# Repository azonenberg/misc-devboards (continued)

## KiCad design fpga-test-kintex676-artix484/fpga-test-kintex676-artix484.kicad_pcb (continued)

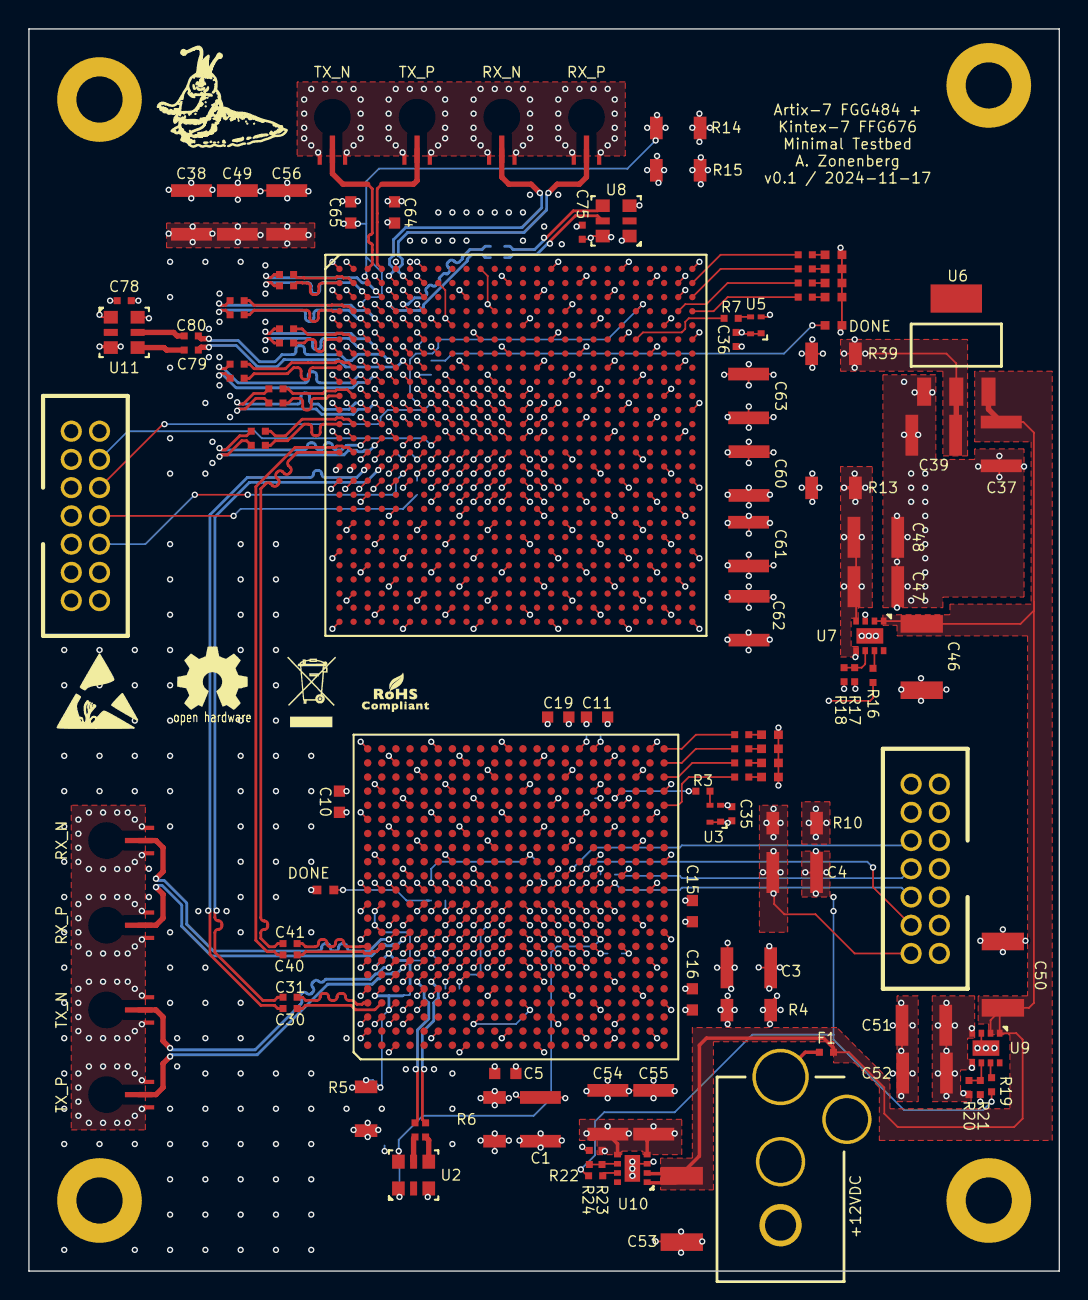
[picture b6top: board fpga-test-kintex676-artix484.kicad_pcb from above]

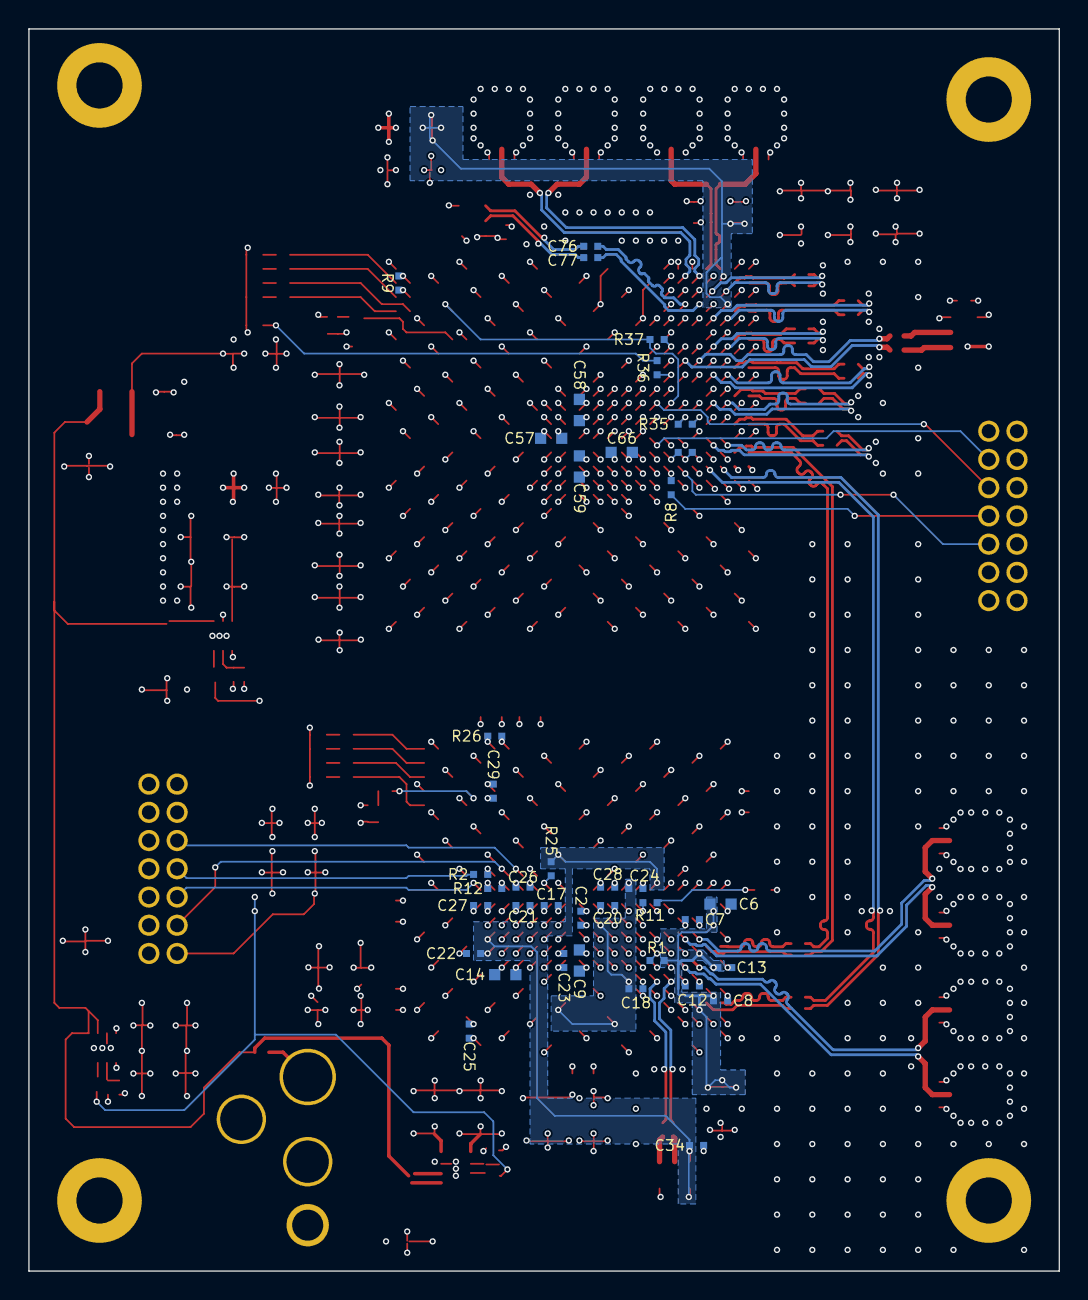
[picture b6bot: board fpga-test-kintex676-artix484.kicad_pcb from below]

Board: 4 copper layers, 73.0 x 88.0 mm, 161 parts (39 on the bottom side), 115 nets.

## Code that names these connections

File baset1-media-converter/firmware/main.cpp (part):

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void InitUART()
{
	//Initialize the UART
	static GPIOPin uart_tx(&GPIOA, 2,	GPIOPin::MODE_PERIPHERAL, 1);
	static GPIOPin uart_rx(&GPIOA, 3, GPIOPin::MODE_PERIPHERAL, 1);
	static UART uart(&USART1, &USART1, 417);
	g_uart = &uart;

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
void InitLEDs()
{
	GPIOPin gpio_led0(&GPIOA, 15, GPIOPin::MODE_OUTPUT);
	GPIOPin gpio_led1(&GPIOB, 3, GPIOPin::MODE_OUTPUT);
	GPIOPin gpio_led2(&GPIOB, 4, GPIOPin::MODE_OUTPUT);
	GPIOPin gpio_led3(&GPIOB, 5, GPIOPin::MODE_OUTPUT);
	gpio_led0 = 0;
	gpio_led1 = 0;
	gpio_led2 = 0;
	gpio_led3 = 0;

	g_led[0] = &gpio_led0;
	g_led[1] = &gpio_led1;
	g_led[2] = &gpio_led2;
	g_led[3] = &gpio_led3;
}

void DetectHardware()
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
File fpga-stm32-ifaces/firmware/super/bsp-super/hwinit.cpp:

/***********************************************************************************************************************
*                                                                                                                      *
* misc-devboards                                                                                                       *
*                                                                                                                      *
* Copyright (c) 2023-2024 Andrew D. Zonenberg and contributors                                                         *
* All rights reserved.                                                                                                 *
*                                                                                                                      *
* Redistribution and use in source and binary forms, with or without modification, are permitted provided that the     *
* following conditions are met:                                                                                        *
*                                                                                                                      *
*    * Redistributions of source code must retain the above copyright notice, this list of conditions, and the         *
*      following disclaimer.                                                                                           *
*                                                                                                                      *
*    * Redistributions in binary form must reproduce the above copyright notice, this list of conditions and the       *
*      following disclaimer in the documentation and/or other materials provided with the distribution.                *
*                                                                                                                      *
*    * Neither the name of the author nor the names of any contributors may be used to endorse or promote products     *
*      derived from this software without specific prior written permission.                                           *
*                                                                                                                      *
* THIS SOFTWARE IS PROVIDED BY THE AUTHORS "AS IS" AND ANY EXPRESS OR IMPLIED WARRANTIES, INCLUDING, BUT NOT LIMITED   *
* TO, THE IMPLIED WARRANTIES OF MERCHANTABILITY AND FITNESS FOR A PARTICULAR PURPOSE ARE DISCLAIMED. IN NO EVENT SHALL *
* THE AUTHORS BE HELD LIABLE FOR ANY DIRECT, INDIRECT, INCIDENTAL, SPECIAL, EXEMPLARY, OR CONSEQUENTIAL DAMAGES        *
* (INCLUDING, BUT NOT LIMITED TO, PROCUREMENT OF SUBSTITUTE GOODS OR SERVICES; LOSS OF USE, DATA, OR PROFITS; OR       *
* BUSINESS INTERRUPTION) HOWEVER CAUSED AND ON ANY THEORY OF LIABILITY, WHETHER IN CONTRACT, STRICT LIABILITY, OR TORT *
* (INCLUDING NEGLIGENCE OR OTHERWISE) ARISING IN ANY WAY OUT OF THE USE OF THIS SOFTWARE, EVEN IF ADVISED OF THE       *
* POSSIBILITY OF SUCH DAMAGE.                                                                                          *
*                                                                                                                      *
***********************************************************************************************************************/

/**
	@file
	@author	Andrew D. Zonenberg
	@brief	Boot-time hardware initialization
 */
#include <core/platform.h>
#include <supervisor/supervisor-common.h>
#include "hwinit.h"
#include <peripheral/Power.h>

void InitSPI();

////////////////////////////////////////////////////////////////////////////////////////////////////////////////////////
// Common global hardware config used by both bootloader and application

//UART console
//USART1 is on APB1 (80 MHz), so we need a divisor of 694.44, round to 694
UART<16, 256> g_uart(&USART1, 694);

//SPI bus to the main MCU
SPI<64, 64> g_spi(&SPI1, true, 2, false);

//I2C1 defaults to running of APB clock (80 MHz)
//Prescale by 4 to get 20 MHz
//Divide by 200 after that to get 100 kHz
I2C g_i2c(&I2C1, 4, 200);

////////////////////////////////////////////////////////////////////////////////////////////////////////////////////////
// Low level init

void BSP_InitUART()
{
	//Initialize the UART for local console: 115.2 Kbps
	//TODO: nice interface for enabling UART interrupts
	GPIOPin uart_tx(&GPIOA, 9, GPIOPin::MODE_PERIPHERAL, GPIOPin::SLEW_SLOW, 7);
	GPIOPin uart_rx(&GPIOA, 10, GPIOPin::MODE_PERIPHERAL, GPIOPin::SLEW_SLOW, 7);

	g_logTimer.Sleep(10);	//wait for UART pins to be high long enough to remove any glitches during powerup

	//Enable the UART interrupt
	NVIC_EnableIRQ(37);
}

////////////////////////////////////////////////////////////////////////////////////////////////////////////////////////
// Common features shared by both application and bootloader

void BSP_Init()
{
	//Bring up the IBC before powering up the rest of the system
	InitGPIOs();
	Super_Init();
	InitSPI();

	App_Init();
}

void InitSPI()
{
	g_log("Initializing management SPI bus\n");

	//Set up GPIOs for management bus
	static GPIOPin mgmt_sck(&GPIOA, 5, GPIOPin::MODE_PERIPHERAL, GPIOPin::SLEW_FAST, 5);
	static GPIOPin mgmt_mosi(&GPIOA, 7, GPIOPin::MODE_PERIPHERAL, GPIOPin::SLEW_FAST, 5);
	static GPIOPin mgmt_cs_n(&GPIOA, 4, GPIOPin::MODE_PERIPHERAL, GPIOPin::SLEW_FAST, 5);
	static GPIOPin mgmt_miso(&GPIOA, 6, GPIOPin::MODE_PERIPHERAL, GPIOPin::SLEW_FAST, 5);

	//Save the CS# pin
	g_spiCS = &mgmt_cs_n;

	//Set up IRQ6 for SPI CS# (PA4) change
	RCCHelper::EnableSyscfg();
	NVIC_EnableIRQ(10);
	EXTI::SetExtInterruptMux(4, EXTI::PORT_A);
	EXTI::EnableChannel(4);
	EXTI::EnableFallingEdgeTrigger(4);

	//Set up IRQ35 as SPI1 interrupt
	NVIC_EnableIRQ(35);
	g_spi.EnableRxInterrupt();
}

////////////////////////////////////////////////////////////////////////////////////////////////////////////////////////
// GPIOs for all of the rail enables

void InitGPIOs()
{
	g_log("Initializing GPIOs\n");

	//Enable pullups on all PGOOD lines
	g_1v0_pgood.SetPullMode(GPIOPin::PULL_UP);
	g_1v2_pgood.SetPullMode(GPIOPin::PULL_UP);
	g_1v8_pgood.SetPullMode(GPIOPin::PULL_UP);
	g_3v3_pgood.SetPullMode(GPIOPin::PULL_UP);

	//turn off all LEDs
	g_pgoodLED = 0;
	g_faultLED = 0;
	g_sysokLED = 0;

	//Set up GPIOs for I2C bus
	static GPIOPin i2c_scl(&GPIOB, 6, GPIOPin::MODE_PERIPHERAL, GPIOPin::SLEW_SLOW, 4, true);
	static GPIOPin i2c_sda(&GPIOB, 7, GPIOPin::MODE_PERIPHERAL, GPIOPin::SLEW_SLOW, 4, true);
}

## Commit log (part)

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2017-09-28 Initial PHY design. Needs decoupling caps for FPGA still.
2017-09-29 Began layout on TRAGICLASER PHY
2017-10-01 Finished initial layout, ready for design review
2017-10-07 Updated a few export settings during design review
2017-10-08 Updated export settings, moved a bit of silkscreen text
2017-10-22 PHY: fixed swapped resistor values
2018-08-27 Initial version of jtag-swd-bridge
2019-01-15 Initial version of ksz9031-eval
2022-03-28 Updated cache
2022-03-28 Initial work on pic32mx-jtag test board
2022-03-29 Finished v0.1 of pic32mx-jtag
2024-01-26 Updated ksz9031 project settings
2024-01-26 Added LTC3374 test board from ages ago
2024-01-26 Added openocd config for pic32 JTAG board
2024-01-26 Initial schematic for baseT1 media converter
2024-01-28 Continued layout on media converter
2024-01-28 Updating file: baset1-media-converter.kicad_pcb with current fully routed design
2024-01-29 Final v0.1 media converter design after layout review
2024-01-29 Updated with export directory for output
2024-02-01 Initial schematic and preliminary layout skeleton for kup-lulz board
2024-02-03 Continued initial work on kup-lulz devboard
2024-02-05 Continued initial layout of kup-lulz
2024-02-06 Continued initial layout
2024-02-06 Continued initial routing
2024-02-07 Continued kup-lulz routing. Deleted one of the PMODs as there's no way it will fit.
2024-02-07 Initial work on power planes, finished hooking up QSFP GPIOs
2024-02-09 FPGA is fully scaped, maybe? just need to hook up MCU now
2024-02-11 Added stm32-cpp submodule
2024-02-11 Added note about incorrect FTDI footprint
2024-02-11 Initial work on baseT1 media converter firmware
2024-02-19 Hopefully-done firmware for 100mbit version of media converter
2024-02-22 baset1-media-converter: initial work on gigabit support in firmware
2024-02-22 kup-lulz: continued initial layout, moved SFP0 GPIOs to be entirely FPGA driven
2024-02-22 Started MCU routing
2024-02-22 Continued MCU fanout
2024-02-22 Updating file: kup-lulz.kicad_pcb with current fully routed design
2024-02-23 Finished resolving all first-pass DRC errors (but not warnings)
2024-02-23 Fully routed and DRC clean, added stitching vias on 5mm grid. Still needs layer-change vias for diffpairs and connector launch optimization
2024-02-23 Silkscreen cleanup, added fan
2024-02-23 Zone fill tweaks, reduced some ref plane split crossings
2024-02-26 Fixed ivnerted IBC management symbol
2024-02-26 Updated ignores
2024-03-15 Initial simulation import
2024-03-15 Removed old kup-lulz sims
2024-05-01 Converted to kicad8 format, updated footprints and 3D models appropriately
2024-05-25 Initial skeleton of fpga-stm32-ifaces
2024-06-11 Finished initial version of symmetricom breakout
2024-06-11 Updated symmetricom breakout after review
2024-06-12 Finished initial schematic of fpga-stm32-ifaces board, waiting for sch review
2024-06-13 Continued initial layout of fpga-stm32-ifaces
2024-06-13 Initial routing of FPGA power
2024-06-13 Routed most FPGA decoupling caps plus most of RGMII
2024-06-14 Continued layout, 283 now unrouted
2024-06-14 Lots more routing around FPGA and MCU
2024-06-14 More FPGA power routing
2024-06-15 Continued fpga-stm32-ifaces layout
2024-06-15 Finished FPGA and MCU escape and interconnect routing
2024-06-18 Finished initial layout, passing DRC
2024-06-18 Lots of routing cleanup
2024-06-18 More routing cleanup
2024-06-19 More routing cleanup ready for layout review
2024-06-19 Finished interface test board, ready to order
2024-06-19 One final routing tweak before ordering
2024-07-07 Initial sch skeleton of lpr-rgmii-phy
2024-07-07 lpr-rgmii-phy: Finished initial layout, ready for review
2024-07-07 Minor changes to layout made during design review
2024-07-07 Added additioanl stitching vias
2024-07-14 Initial version of fpga-stm32-ifaces firmware for supervisor and FPGA blinky
2024-07-16 Initial FMC test is functional on reads without any wait state testing
2024-07-16 Test firmware is happy with FMC reading constant magic cafebabe
2024-07-19 Initial FMC test firmware is now pingable
2024-07-19 Enabled DTS in test firmware, removed a lot of irrelevant code copied from crossbar
2024-07-19 Initial version of DemoUDPProtocol with NTP client
2024-07-19 Initial test firmware has a CLI now
2024-07-21 Initial iperf benchmark test
2024-07-21 Continued clock optimization tweaks
2024-07-23 Test is now working again at 125 MHz
2024-07-24 Greatly improved iperf performance by moving Ethernet frame buffers and related key state to DTCM
2024-07-26 Increased FMC clock rate from 125 to 137.5 MHz (10% increase). Only 4 Mbps iperf throughput increase (284 -> 288 Mbps) suggesting we're still MCU-bound.
2024-07-27 Initial DMA support for TX
2024-07-28 Initial version of solder paste test board
2024-07-28 Initial test version of paste-test board ready for fab
2024-07-31 imagesize: report ITCM usage
2024-07-31 Updated submodules
2024-07-31 Build: enable hard float if available, add "free" to list of blocked symbols
2024-07-31 Removed ISR attribute (not needed on v7-m and causes warnings about floating point)
2024-08-05 Changed IBC 12V enable power polarity now that we're not using the ancient prototype anymore
2024-08-06 Initial orbtrace experiments
2024-08-07 Began ITM refactoring to stm32-cpp wrappers
2024-08-07 Cleaner DWT setup
2024-08-09 Initial work on IBC I2C integration
2024-08-10 Saving WIP code to use TPIU for 4 bit trace that doesn't actually work
2024-08-10 I2C state machine now fully resets if we lose contact with IBC
2024-08-11 Initial orbtrace-to-xilinx-jtag adapter
2024-08-11 Added logic for reading more IBC sensors
2024-08-11 Initial supervisor - main MCU SPI communication is working, not fully featured. Additional checks for I2C derpiness on startup between supervisor and IBC.
2024-08-11 Initial MCU - supervisor link is up
2024-08-11 Removed 2 sec boot delay now that FPGA link is working reliably
2024-08-11 Increased wait time for supervisor reads
2024-08-12 Moved TempSensorReader to common-embedded-platform
2024-08-14 More refactoring of supervisor code towards data driven architecture
2024-08-14 Fixed bug where during re-sequencing of resets, not all resets would be properly asserted
2024-08-14 System-OK LED now blinks during boot
2024-08-15 Added ETL submodule
2024-08-16 Continued refactoring supervisor code into library
2024-08-16 Moved more stuff to common base
2024-08-17 Redid directory structure so we have one folder per micro
2024-08-17 More directory renaming
2024-08-17 Supervisor is now building under CMake
2024-08-17 Renamed bsp folder
2024-08-17 Main MCU firmware now compiles under CMake
2024-08-17 Removed legacy build script
2024-08-17 Added XADC wrapper core
2024-08-17 Fixed incorrect DTS frequency
2024-08-23 Updated orbuculum scripts
2024-10-06 Initial version of led-test board
2024-11-11 Replaced supervisor with L431
2024-11-11 Continued MCU routing
2024-11-11 Finished initial routing of new processor
2024-11-12 Lots of power routing cleanup under MCU plus stitching vias around diffpairs
2024-11-13 Final kup-lulz design ready for fab
2024-11-13 Final export for fab
2024-11-16 Initial version of christmas-tree
2024-11-16 Switch to larger vias for cheap fab
2024-11-16 DRC tweaks
2024-11-16 Final version ordered
2024-11-16 Removed stale todo comment from schematic
2024-11-17 Initial version of fpga-test-kintex676-artix484
2024-11-17 Finished fpga test
2024-11-20 Initial christmas tree firmware
2024-11-22 Initial serial console support
2024-11-22 Tree now supports selecting one of several light patterns and can persist them to flash
2025-01-06 Updated submodules to latest upstream
2025-01-08 Initial bringup work on kup-lulz
2025-01-24 25G PRBS test is now working for TX
2025-01-24 Testbed bitstream is able to use GTY from QPLL but CPLL needs more troubleshooting, save for much later
2025-02-08 Continued building GTY APB bridge
2025-02-14 Initial kup-lulz SCCB testbed
2025-02-14 Initial SCCB is working in hardware
2025-02-14 Artix GTP RX buffer bypass
2025-02-15 Moved aligner into separate module
2025-03-02 Initial version of qsfp-to-arc6
2025-03-12 Continued SCCB bringup on LATENTRED testbed
2025-04-06 Now have 10Gbase-R RX working, time to start TX
2025-05-02 More work on kup-lulz axi ethernet
2025-05-04 kup-lulz is now pingable over APB AXI
2025-05-07 Continued QSGMII stuff, now functional for RX path
2025-05-12 Continued switch tinkering
2025-05-12 Refactoring: moved APB1/APB2 peripherals to separate modules
2025-05-16 Initial work on switch fabric integration
2025-05-19 Began work on setting up QSFP quad
2025-05-20 Hooked up second GTY quad to kup-lulz LATENTRED testbed
2025-05-21 Removed redundant CDCs, some constraints cleanup
2025-05-22 Initial work on mac table integration
2025-05-24 Ready for hardware testing of LineCardInputBuffering
2025-05-27 Updated CDC constraints and some debug stuff
2025-05-28 Updated kup-lulz config
2025-08-01 Initial version of pip-test
